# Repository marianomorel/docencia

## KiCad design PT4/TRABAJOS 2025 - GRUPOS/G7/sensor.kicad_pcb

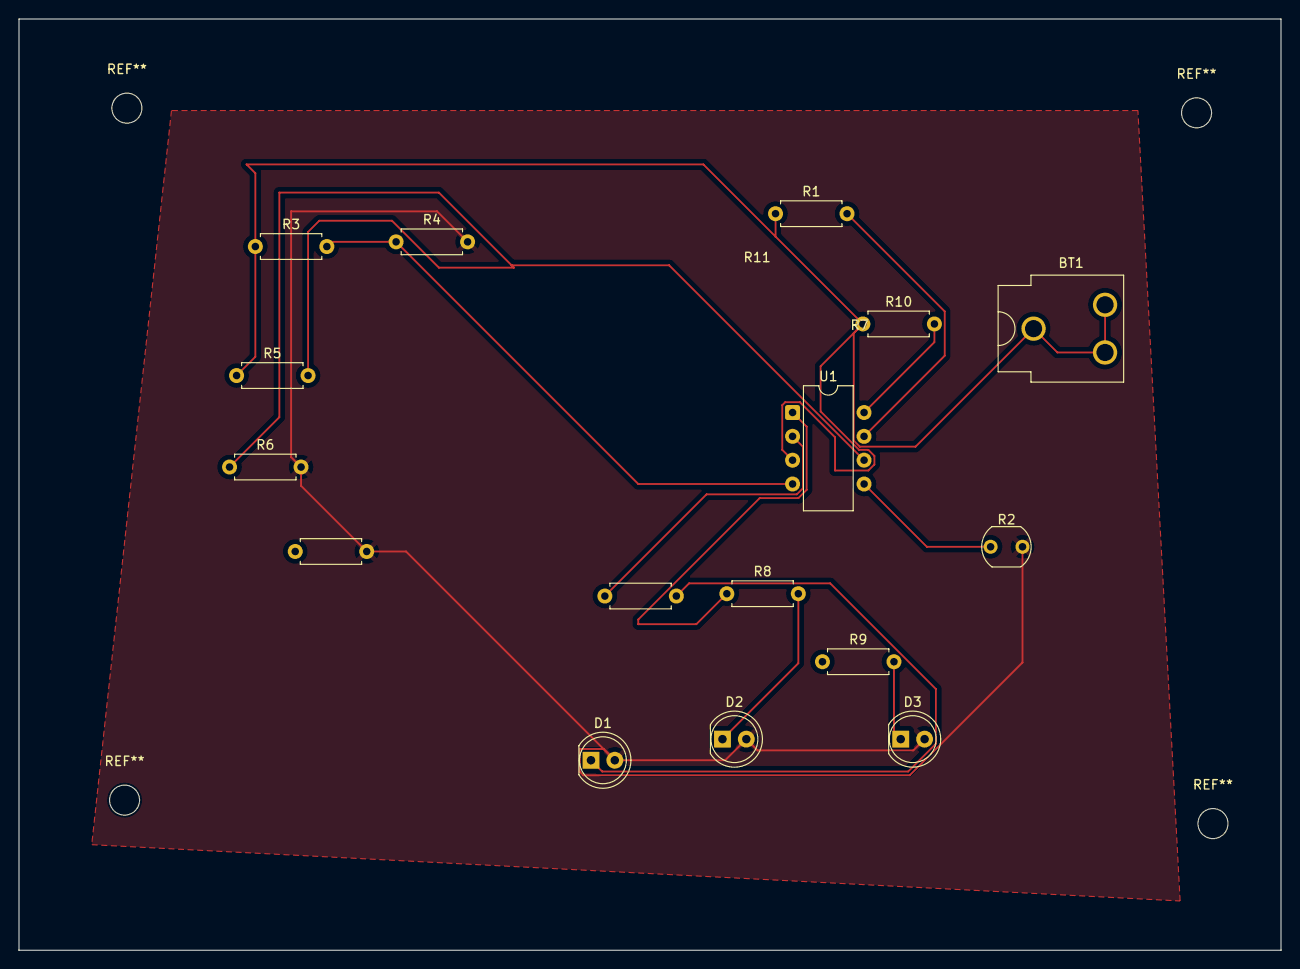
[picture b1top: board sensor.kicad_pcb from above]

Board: 2 copper layers, 134.5 x 99.2 mm, 16 parts (0 on the bottom side), 11 nets.

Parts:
BT1: Battery; BatteryClip_Keystone_54_D16-19mm
D1, D2, D3: LED; LED_D5.0mm
R1, R3, R4, R5, R6, R7, R8, R9, R10, R11: R; R_Axial_DIN0207_L6.3mm_D2.5mm_P7.62mm_Horizontal
R2: LDR07; R_LDR_5.1x4.3mm_P3.4mm_Vertical
U1: LM339; CERDIP-8_W7.62mm_SideBrazed

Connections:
Earth: D1.2 (A), D2.2 (A), D3.2 (A), R2.2, R4.2, R6.2, R11.2
unnamed: BT1.1 (+), R1.1, R3.1, R5.1, R10.1, U1.3 (V+)
unnamed: D1.1 (K), R7.2
unnamed: D2.1 (K), R8.2
unnamed: D3.1 (K), R9.2
unnamed: R7.1, U1.2
unnamed: R8.1, U1.1
unnamed: R1.2, R2.1, U1.5 (+), U1.7 (+)
unnamed: R3.2, R4.1, U1.4 (-)
unnamed: R5.2, R6.1, U1.6 (-)
unnamed: R10.2, U1.8 (-)

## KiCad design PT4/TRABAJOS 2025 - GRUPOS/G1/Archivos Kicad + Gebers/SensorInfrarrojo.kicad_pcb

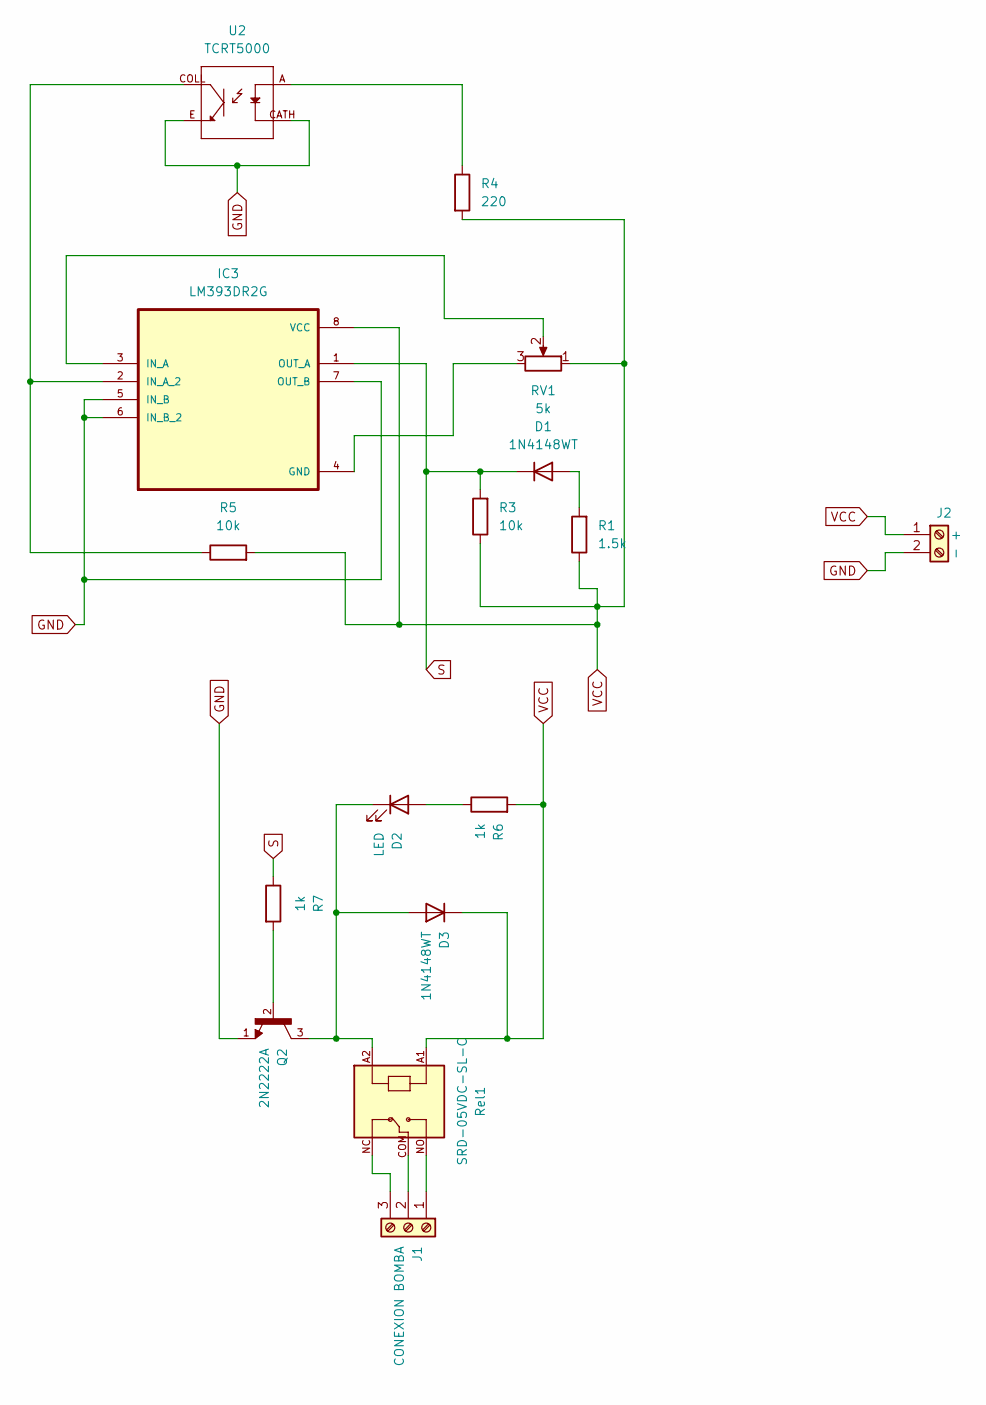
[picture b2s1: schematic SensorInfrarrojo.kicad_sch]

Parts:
D1, D3: 1N4148WT; D_SOD-523
D2: LED; LED_0402_1005Metric_Pad0.77x0.64mm_HandSolder
IC3: LM393DR2G; SOIC127P600X265-8N
J1: CONEXION BOMBA; TerminalBlock_Phoenix_MKDS-1,5-3_1x03_P5.00mm_Horizontal
J2: - +; TerminalBlock_MaiXu_MX126-5.0-02P_1x02_P5.00mm
Q2: 2N2222A; TO92254P470H750-3; PARTREV N/A
R1: 1.5k; R_0603_1608Metric_Pad0.98x0.95mm_HandSolder
R3, R5: 10k; R_0603_1608Metric_Pad0.98x0.95mm_HandSolder
R4: 220; R_0603_1608Metric_Pad0.98x0.95mm_HandSolder
R6, R7: 1k; R_Axial_DIN0204_L3.6mm_D1.6mm_P5.08mm_Horizontal
RV1: 5k; Potentiometer_Bourns_3296W_Vertical
Rel1: SRD-05VDC-SL-C; RELAY_SRD-05VDC-SL-C
U2: TCRT5000; OPTO_TCRT5000; PARTREV 1.7

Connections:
GND: IC3.5 (IN_B), IC3.6 (IN_B_2), IC3.7 (OUT_B), J2.2, Q2.1, U2.CATH, U2.E
unnamed: D1.2 (A), R1.2
unnamed: D2.2 (A), R6.1
unnamed: D2.1 (K), D3.2 (A), Q2.3, Rel1.A2
unnamed: IC3.4 (GND), RV1.3
unnamed: IC3.3 (IN_A), RV1.2
unnamed: IC3.2 (IN_A_2), R5.1, U2.COLL
unnamed: J1.1, Rel1.NO
unnamed: J1.2, Rel1.COM
unnamed: J1.3, Rel1.NC
unnamed: Q2.2, R7.2
unnamed: R4.1, U2.A
S: D1.1 (K), IC3.1 (OUT_A), R3.2, R7.1
VCC: D3.1 (K), IC3.8 (VCC), J2.1, R1.1, R3.1, R4.2, R5.2, R6.2, RV1.1, Rel1.A1

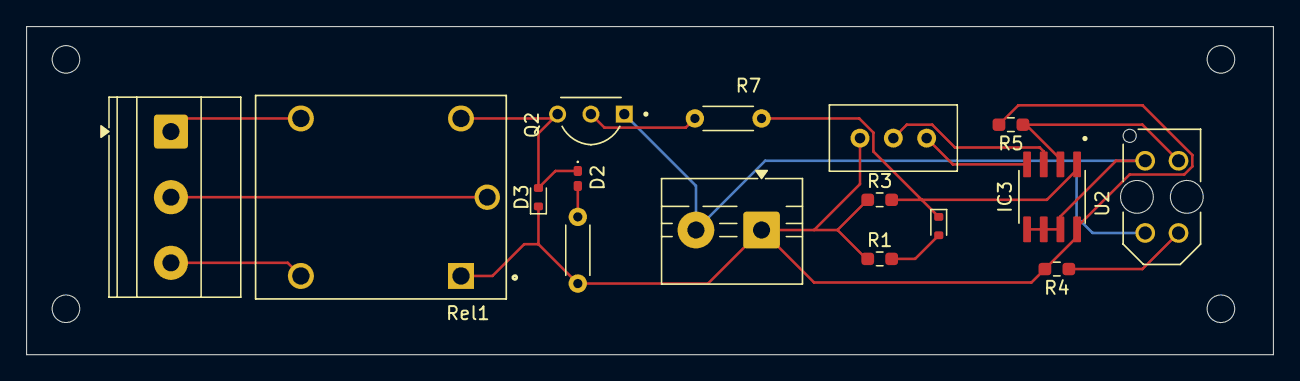
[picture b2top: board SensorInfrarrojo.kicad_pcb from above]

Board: 2 copper layers, 95.0 x 25.0 mm, 16 parts (0 on the bottom side), 14 nets.

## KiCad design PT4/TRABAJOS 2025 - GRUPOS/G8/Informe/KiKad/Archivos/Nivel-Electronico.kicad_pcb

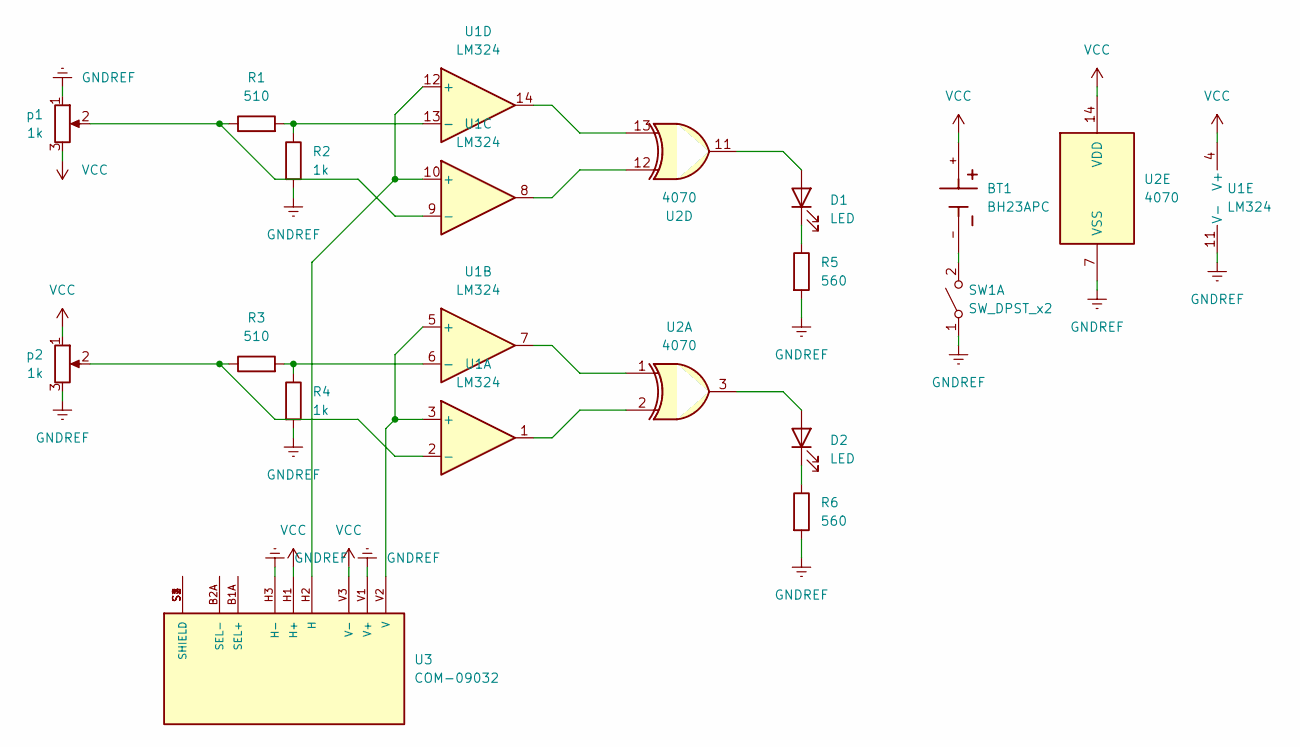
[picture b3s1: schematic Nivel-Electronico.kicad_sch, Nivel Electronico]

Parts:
BT1: BH23APC; BAT_BH23APC
D1, D2: LED; LED_D5.0mm
R1, R3: 510; R_Axial_DIN0204_L3.6mm_D1.6mm_P5.08mm_Vertical
R2, R4: 1k; R_Axial_DIN0204_L3.6mm_D1.6mm_P5.08mm_Vertical
R5, R6: 560; R_Axial_DIN0204_L3.6mm_D1.6mm_P5.08mm_Vertical
SW1: SW_DPST_x2; SW_Push_2P2T_Toggle_CK_PVA2OAH5xxxxxxV2
U1: LM324; DIP-14_W7.62mm_LongPads
U2: 4070; DIP-14_W7.62mm_LongPads
U3: COM-09032; XDCR_COM-09032
p1, p2: 1k; Potentiometer_ACP_CA9-V10_Vertical

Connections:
GNDREF: R2.2, R4.2, R5.2, R6.2, SW1.1 (A), U1.11 (V-), U2.7 (VSS), U3.H3 (H-), U3.V1 (V+), p1.1, p2.3
unnamed: D1.2 (A), U2.11
unnamed: D1.1 (K), R5.1
unnamed: D2.2 (A), U2.3
unnamed: D2.1 (K), R6.1
unnamed: BT1.-, SW1.2 (B)
unnamed: U1.1, U2.2
unnamed: U1.7, U2.1
unnamed: U1.8, U2.12
unnamed: U1.14, U2.13
unnamed: U1.3 (+), U1.5 (+), U3.V2 (V)
unnamed: R3.1, U1.2 (-), p2.2
unnamed: R3.2, R4.1, U1.6 (-)
unnamed: U1.10 (+), U1.12 (+), U3.H2 (H)
unnamed: R1.1, U1.9 (-), p1.2
unnamed: R1.2, R2.1, U1.13 (-)
unnamed: U3.S1 (SHIELD), U3.S2 (SHIELD), U3.S3 (SHIELD), U3.S4 (SHIELD)
VCC: BT1.+, U1.4 (V+), U2.14 (VDD), U3.H1 (H+), U3.V3 (V-), p1.3, p2.1

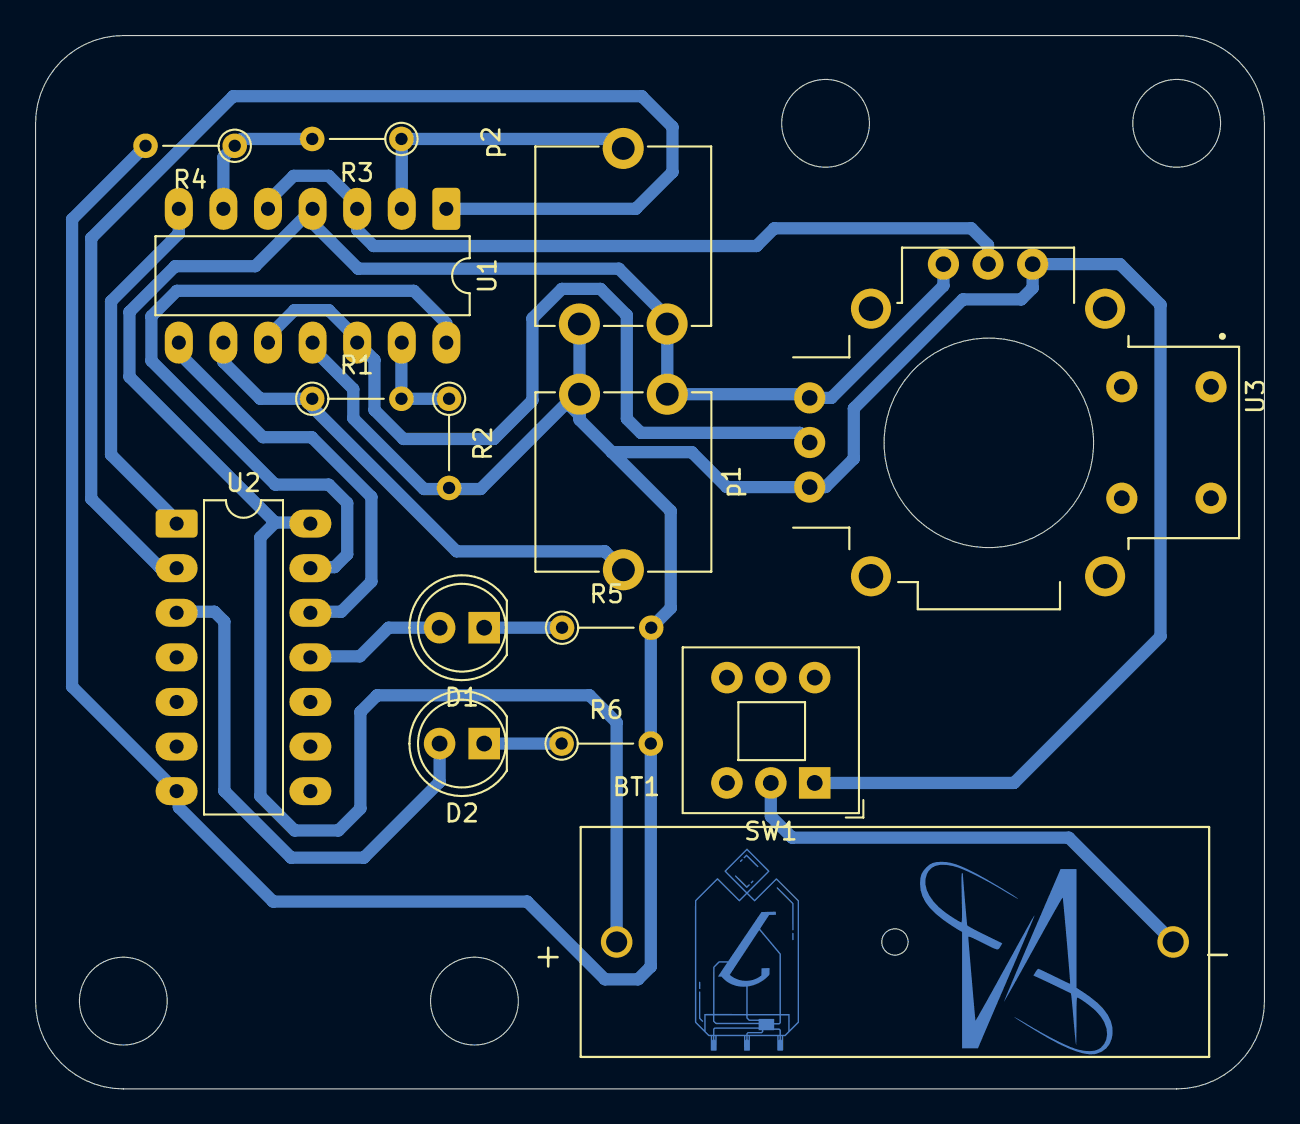
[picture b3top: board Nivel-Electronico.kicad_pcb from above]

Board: 2 copper layers, 70.0 x 60.0 mm, 15 parts (0 on the bottom side), 18 nets.

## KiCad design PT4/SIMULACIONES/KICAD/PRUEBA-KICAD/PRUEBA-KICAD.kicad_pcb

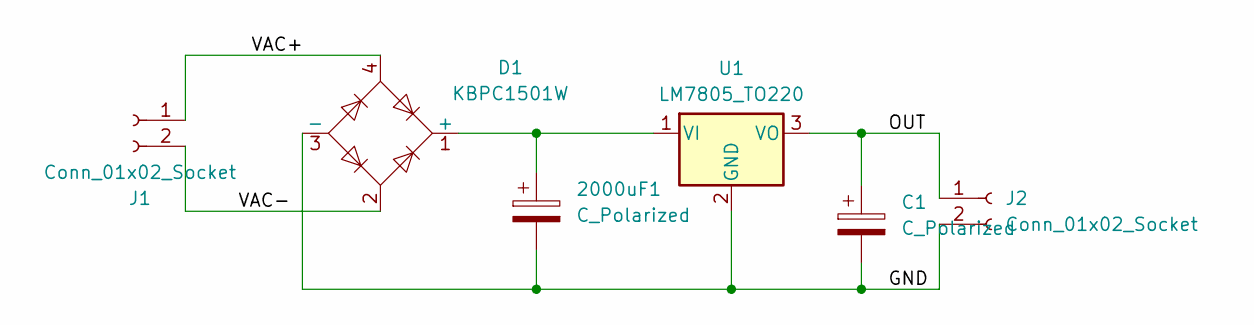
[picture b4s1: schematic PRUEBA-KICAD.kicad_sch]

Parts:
2000uF1: C_Polarized; C_Radial_D18.0mm_H35.5mm_P7.50mm
C1: C_Polarized; C_Radial_D5.0mm_H11.0mm_P2.00mm
D1: KBPC1501W; Diode_Bridge_GeneSiC_KBPC_W
J1, J2: Conn_01x02_Socket; TerminalBlock_MaiXu_MX126-5.0-02P_1x02_P5.00mm
U1: LM7805_TO220; TO-220-3_Vertical

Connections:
/GND: 2000uF1.2, C1.2, D1.3 (-), J2.2, U1.2 (GND)
/OUT: C1.1, J2.1, U1.3 (VO)
/VAC+: D1.4, J1.1
/VAC-: D1.2, J1.2
unnamed: 2000uF1.1, D1.1 (+), U1.1 (VI)

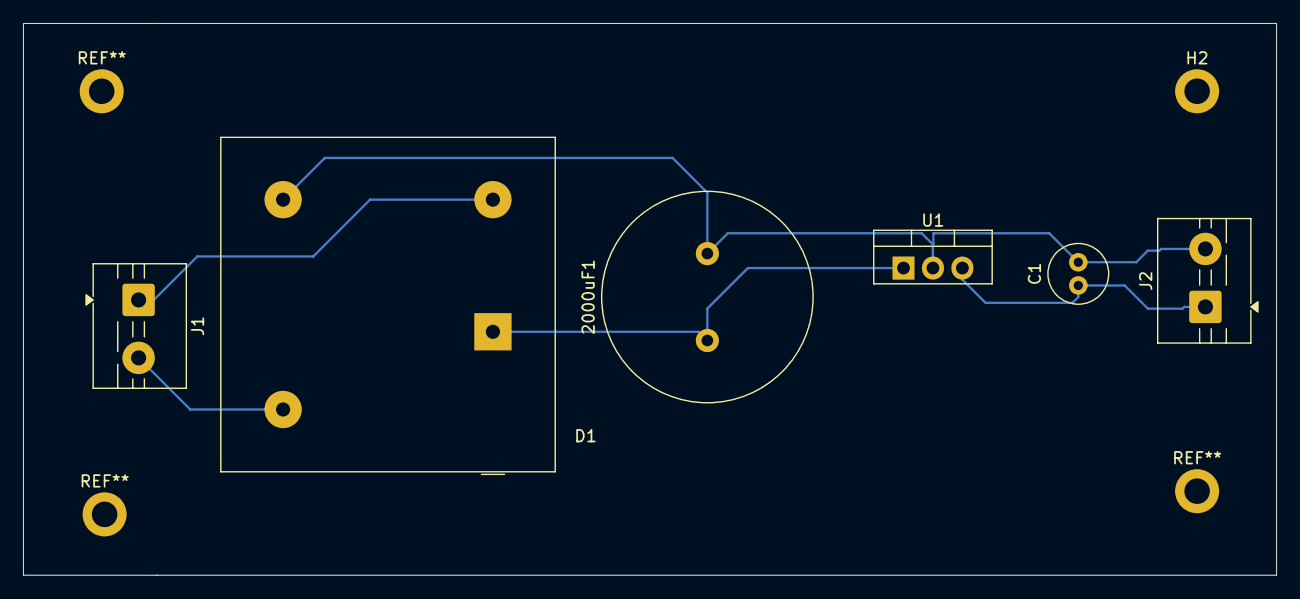
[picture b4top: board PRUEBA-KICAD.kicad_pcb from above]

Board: 2 copper layers, 108.1 x 47.6 mm, 7 parts (0 on the bottom side), 5 nets.

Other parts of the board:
H2: MountingHole_2.2mm_M2_DIN965_Pad

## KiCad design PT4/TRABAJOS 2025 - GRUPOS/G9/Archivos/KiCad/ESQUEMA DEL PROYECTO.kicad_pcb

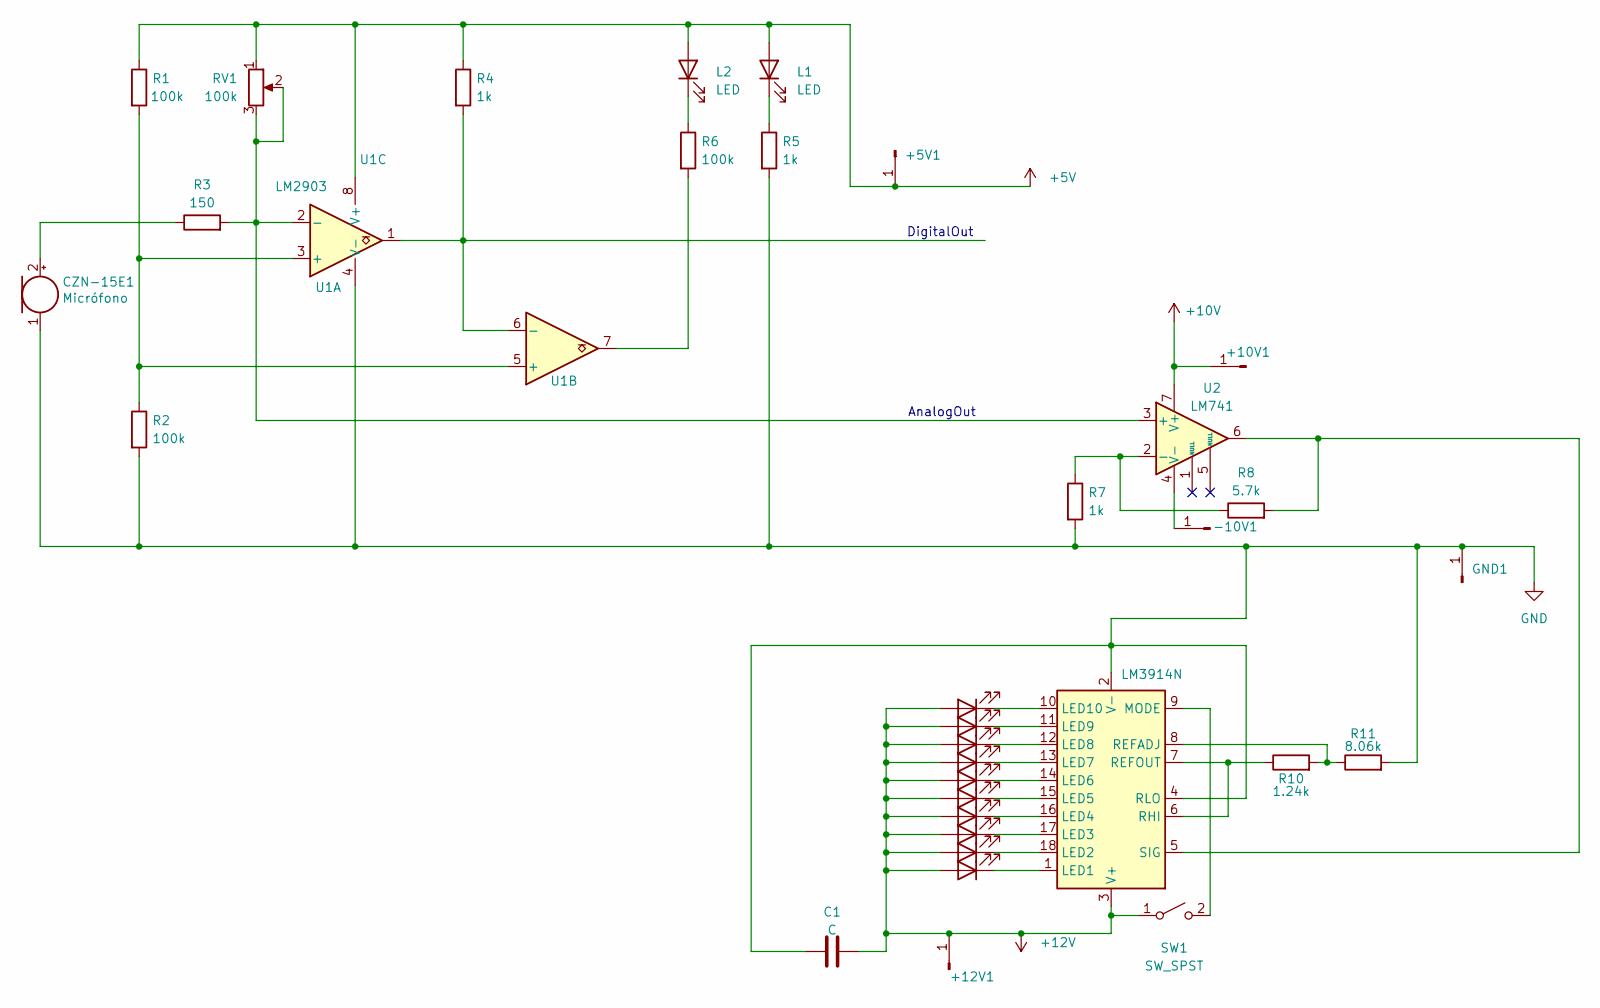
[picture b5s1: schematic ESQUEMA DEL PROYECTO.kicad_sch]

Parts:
+5V1, +10V1, +12V1: Conn_01x01_Pin; TestPoint_Pad_D3.0mm
-10V1: Conn_01x01_Pin; TestPoint_Pad_D3.0mm
C1: C; CP_EIA-1608-08_AVX-J
CZN-15E1: Micrófono; POM-2244P-C3310-2-R
GND1: Conn_01x01_Pin; TestPoint_Pad_D3.0mm
L1, L2, L3, L4, L5, L6, L7, L8, L9, L10, L11, L12: LED; LED_0603_1608Metric
R1, R2, R6: 100k; R_0805_2012Metric
R3: 150; R_0805_2012Metric
R4, R5, R7: 1k; R_0805_2012Metric
R8: 5.7k; R_0805_2012Metric
R10: 1.24k; R_0805_2012Metric
R11: 8.06k; R_0805_2012Metric
RV1: 100k; Potentiometer_Bourns_3296X_Horizontal
SW1: SW_SPST; SW_SPST_TL3342
U1: LM2903; DIP-8_W7.62mm
U2: LM741; DIP-8_W7.62mm
U3: LM3914N; DIP-18_W7.62mm

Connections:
+5V: +5V1.1, L1.2 (A), L2.2 (A), R1.1, R4.1, RV1.1, U1.8 (V+)
+10V: +10V1.1, U2.7 (V+)
+12V: +12V1.1, C1.2, L3.2 (A), L4.2 (A), L5.2 (A), L6.2 (A), L7.2 (A), L8.2 (A), L9.2 (A), L10.2 (A), L11.2 (A), L12.2 (A), SW1.1 (A), U3.3 (V+)
GND: C1.1, CZN-15E1.1 (-), GND1.1, R2.2, R5.2, R7.2, R11.2, U1.4 (V-), U3.2 (V-), U3.4 (RLO)
unnamed: -10V1.1, U2.4 (V-)
unnamed: CZN-15E1.2 (+), R3.1
unnamed: L1.1 (K), R5.1
unnamed: L2.1 (K), R6.1
unnamed: L3.1 (K), U3.1 (LED1)
unnamed: L4.1 (K), U3.18 (LED2)
unnamed: L5.1 (K), U3.17 (LED3)
unnamed: L6.1 (K), U3.16 (LED4)
unnamed: L7.1 (K), U3.15 (LED5)
unnamed: L8.1 (K), U3.14 (LED6)
unnamed: L9.1 (K), U3.13 (LED7)
unnamed: L10.1 (K), U3.12 (LED8)
unnamed: L11.1 (K), U3.11 (LED9)
unnamed: L12.1 (K), U3.10 (LED10)
unnamed: R6.2, U1.7
unnamed: SW1.2 (B), U3.9 (MODE)
unnamed: R1.2, R2.1, U1.3 (+), U1.5 (+)
unnamed: R3.2, RV1.2, RV1.3, U1.2 (-), U2.3 (+)
unnamed: R4.2, U1.1, U1.6 (-)
unnamed: R7.1, R8.1, U2.2 (-)
unnamed: R10.2, R11.1, U3.8 (REFADJ)
unnamed: R10.1, U3.6 (RHI), U3.7 (REFOUT)
unnamed: R8.2, U2.6, U3.5 (SIG)

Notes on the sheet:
AnalogOut
DigitalOut

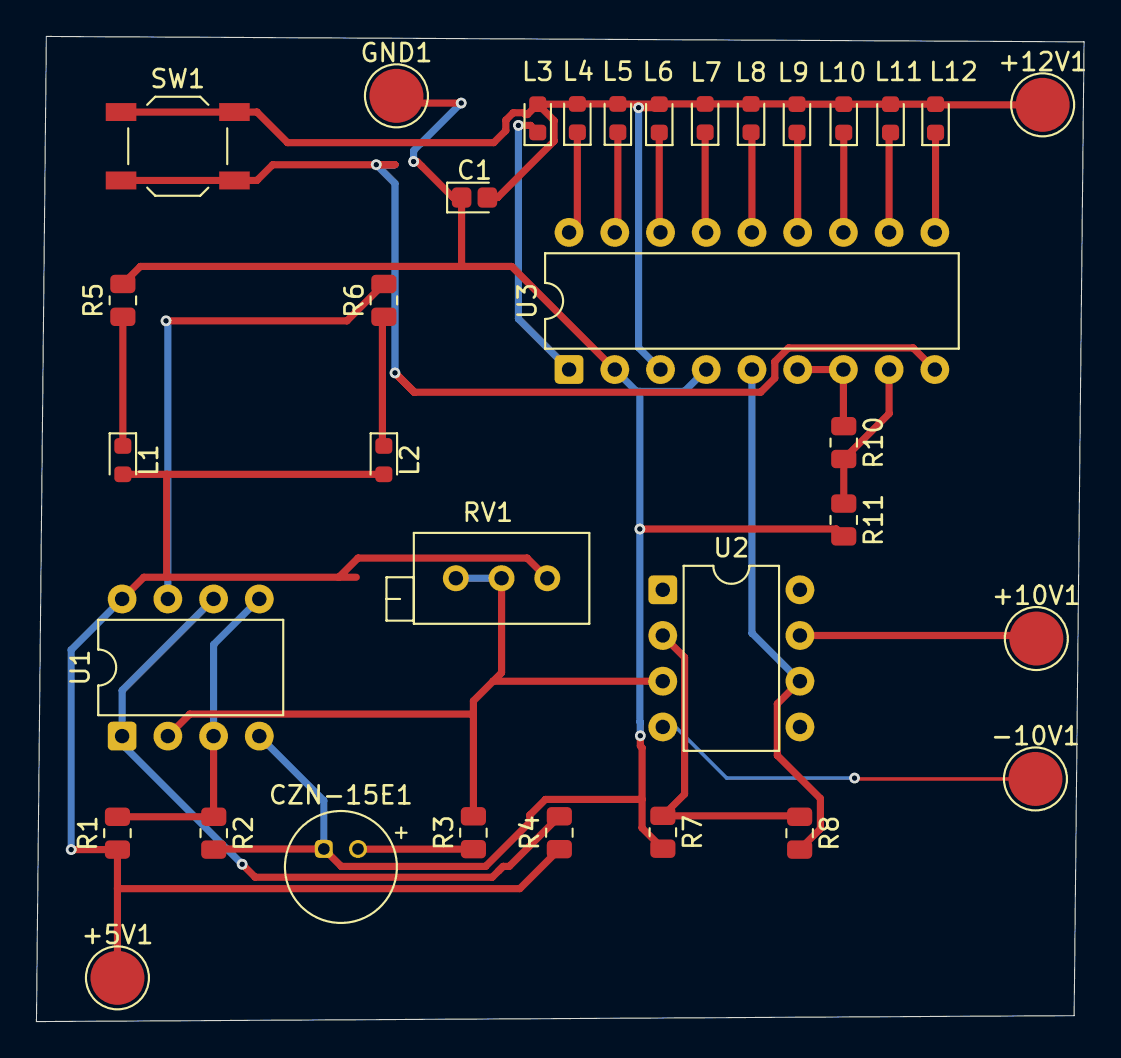
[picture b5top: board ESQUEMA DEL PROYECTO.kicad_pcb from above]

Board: 2 copper layers, 58.2 x 54.7 mm, 34 parts (0 on the bottom side), 27 nets.

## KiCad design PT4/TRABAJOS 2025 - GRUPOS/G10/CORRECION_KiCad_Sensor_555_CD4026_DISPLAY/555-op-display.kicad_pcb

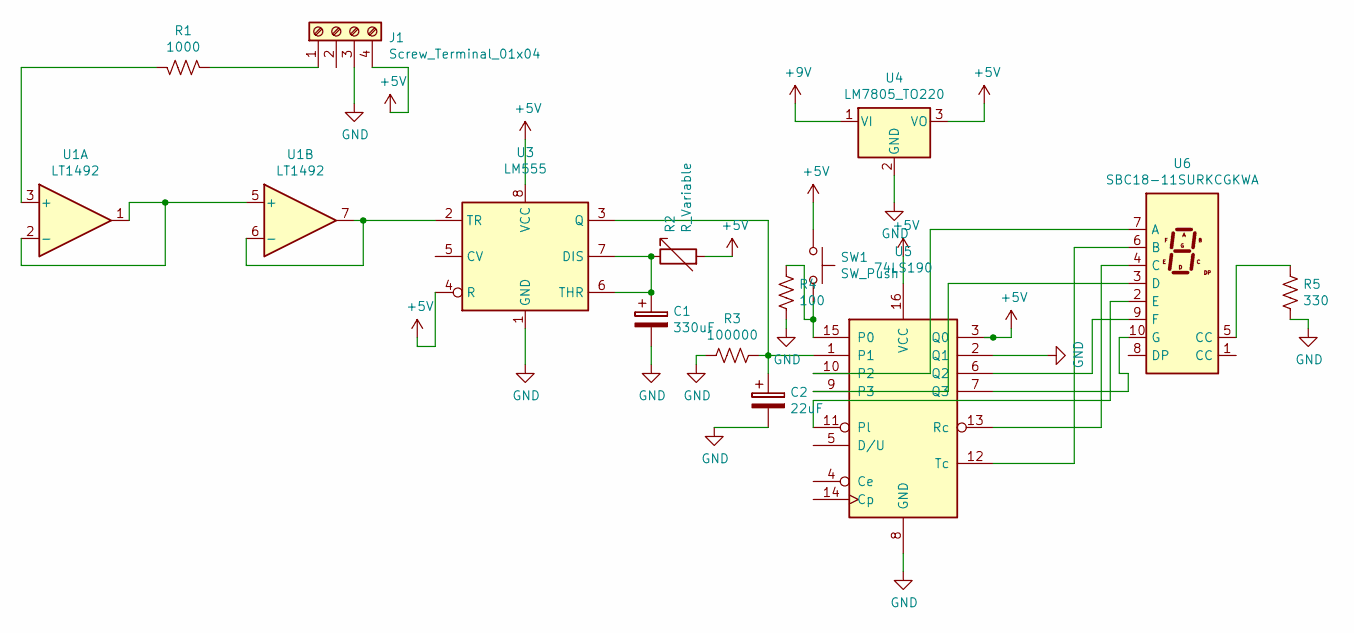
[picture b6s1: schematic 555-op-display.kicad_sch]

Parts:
C1: 330uF; CP_Radial_D5.0mm_P2.50mm
C2: 22uF; CP_Radial_D5.0mm_P2.50mm
J1: Screw_Terminal_01x04; TerminalBlock_bornier-4_P5.08mm
R1: 1000; R_Axial_DIN0204_L3.6mm_D1.6mm_P5.08mm_Horizontal
R2: R_Variable; Potentiometer_Trimmer_ACP_CA6v_Horizontal
R3: 100000; R_Axial_DIN0207_L6.3mm_D2.5mm_P7.62mm_Horizontal
R4: 100; R_Axial_DIN0207_L6.3mm_D2.5mm_P7.62mm_Horizontal
R5: 330; R_Axial_DIN0207_L6.3mm_D2.5mm_P7.62mm_Horizontal
SW1: SW_Push; KSA_Tactile_SPST
U1: LT1492; DIP-8_W7.62mm
U3: LM555; DIP-8_W7.62mm
U4: LM7805_TO220; TO-220-3_Vertical
U5: 74LS190; DIP-16_W7.62mm
U6: SBC18-11SURKCGKWA; 7SEGMENT-LED__HDSM531_HDSM533_SMD

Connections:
+5V: J1.4, R2.2, SW1.1, U3.4 (R), U3.8 (VCC), U4.3 (VO), U5.3 (Q0), U5.16 (VCC)
+9V: U4.1 (VI)
GND: C1.2, C2.2, J1.3, R3.2, R4.2, R5.2, U3.1 (GND), U4.2 (GND), U5.2 (Q1), U5.8 (GND)
unnamed: J1.1, R1.1
unnamed: R5.1, U6.5 (CC)
unnamed: R1.2, U1.3 (+)
unnamed: U1.1, U1.2 (-), U1.5 (+)
unnamed: U1.6 (-), U1.7, U3.2 (TR)
unnamed: C1.1, R2.1, U3.6 (THR), U3.7 (DIS)
unnamed: C2.1, R3.1, U3.3 (Q), U5.1
unnamed: R4.1, SW1.2, U5.15 (P0)
unnamed: U5.10 (P2), U6.7 (A)
unnamed: U5.9 (P3), U6.3 (D)
unnamed: U5.11 (Pl), U6.2 (E)
unnamed: U5.6 (Q2), U6.9 (F)
unnamed: U5.7 (Q3), U6.10 (G)
unnamed: U5.13 (Rc), U6.4 (C)
unnamed: U5.12 (Tc), U6.6 (B)

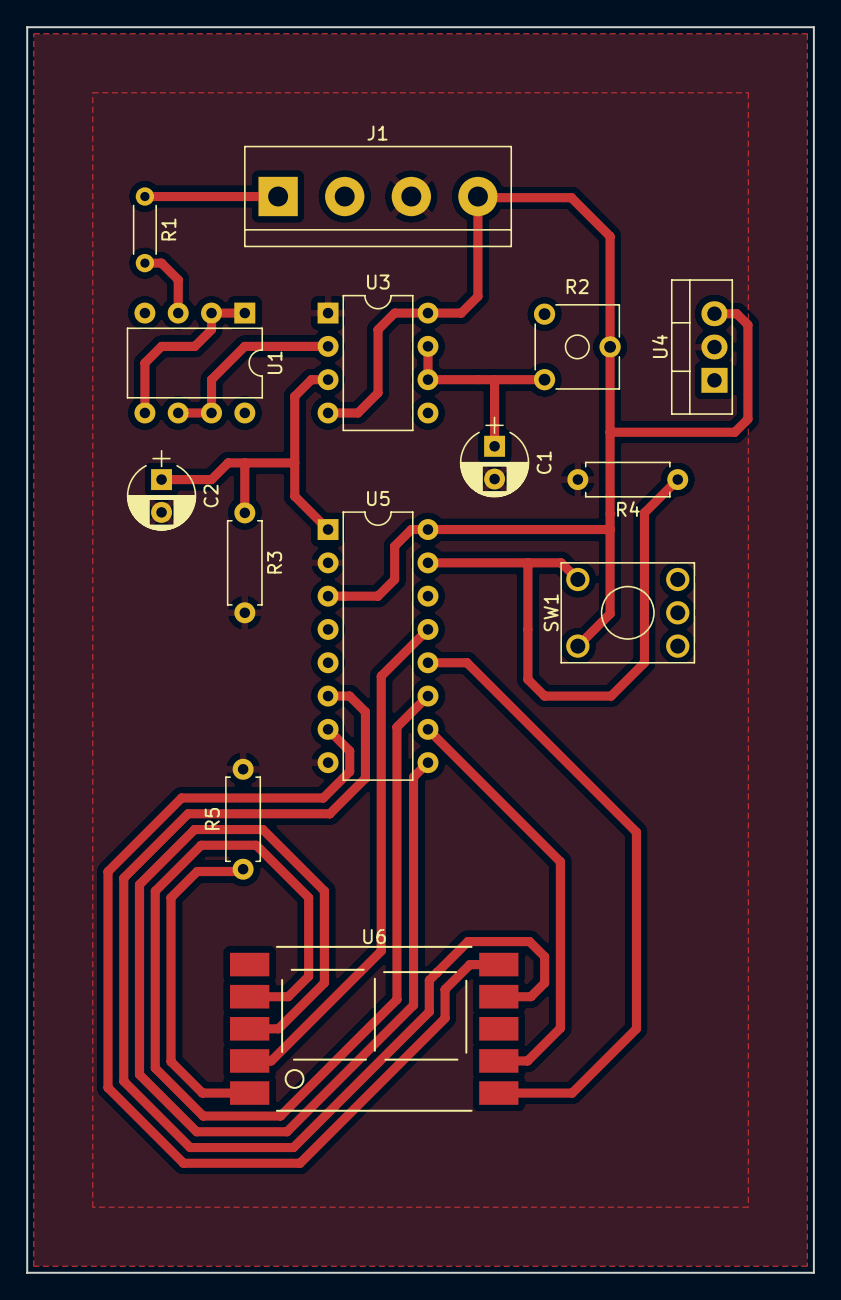
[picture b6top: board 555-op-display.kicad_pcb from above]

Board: 2 copper layers, 60.0 x 95.0 mm, 14 parts (0 on the bottom side), 17 nets.

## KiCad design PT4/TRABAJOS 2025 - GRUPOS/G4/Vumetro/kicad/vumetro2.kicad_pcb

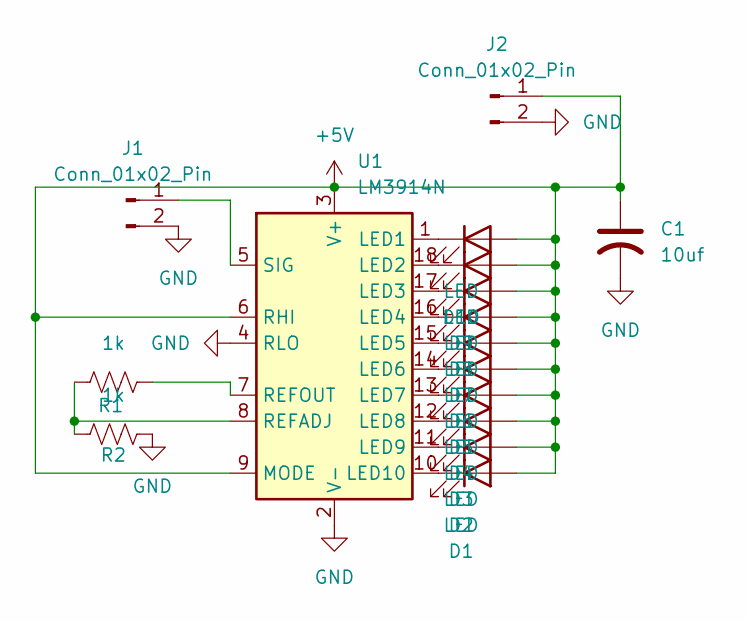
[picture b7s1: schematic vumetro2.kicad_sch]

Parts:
C1: 10uf; CP_Radial_D5.0mm_P2.00mm
D1, D2, D3, D4, D5, D6, D7, D8, D9, D10: LED; LED_D3.0mm_FlatTop
J1, J2: Conn_01x02_Pin; TerminalBlock_4Ucon_1x02_P3.50mm_Horizontal
R1, R2: 1k; R_Axial_DIN0204_L3.6mm_D1.6mm_P5.08mm_Horizontal
U1: LM3914N; DIP-18_W7.62mm

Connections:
+5V: C1.1, D1.2 (A), D2.2 (A), D3.2 (A), D4.2 (A), D5.2 (A), D6.2 (A), D7.2 (A), D8.2 (A), D9.2 (A), D10.2 (A), J2.1, U1.3 (V+), U1.6 (RHI), U1.9 (MODE)
GND: C1.2, J1.2, J2.2, R2.2, U1.2 (V-), U1.4 (RLO)
unnamed: D1.1 (K), U1.10 (LED10)
unnamed: D2.1 (K), U1.11 (LED9)
unnamed: D3.1 (K), U1.12 (LED8)
unnamed: D4.1 (K), U1.13 (LED7)
unnamed: D5.1 (K), U1.14 (LED6)
unnamed: D6.1 (K), U1.15 (LED5)
unnamed: D7.1 (K), U1.16 (LED4)
unnamed: D8.1 (K), U1.17 (LED3)
unnamed: D9.1 (K), U1.18 (LED2)
unnamed: D10.1 (K), U1.1 (LED1)
unnamed: J1.1, U1.5 (SIG)
unnamed: R1.1, R2.1, U1.8 (REFADJ)
unnamed: R1.2, U1.7 (REFOUT)

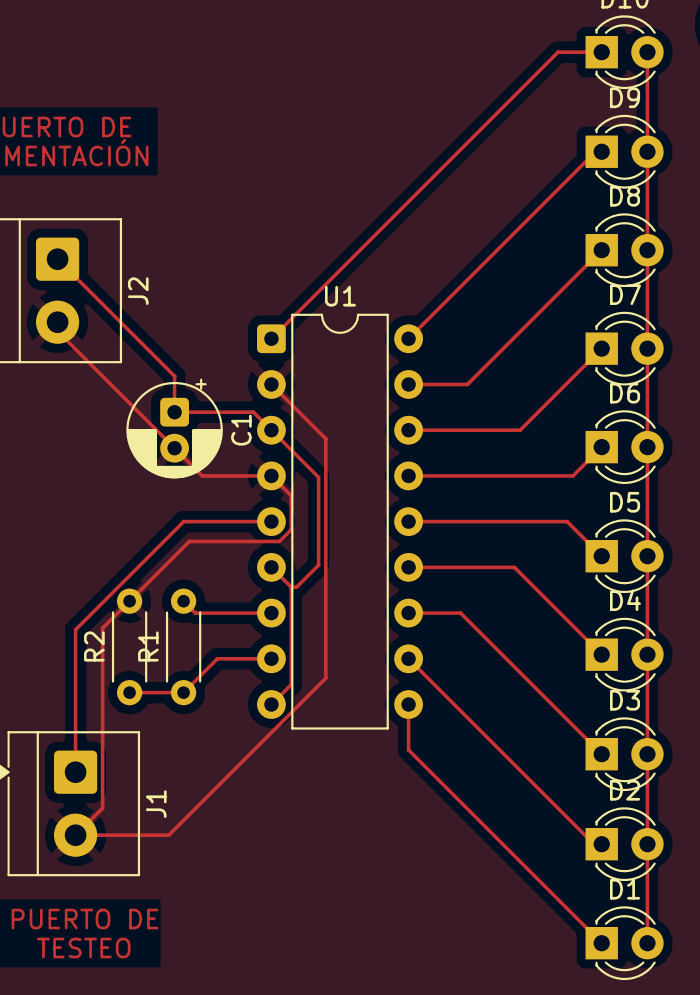
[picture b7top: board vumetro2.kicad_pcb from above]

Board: 2 copper layers, 16 parts (0 on the bottom side), 15 nets.

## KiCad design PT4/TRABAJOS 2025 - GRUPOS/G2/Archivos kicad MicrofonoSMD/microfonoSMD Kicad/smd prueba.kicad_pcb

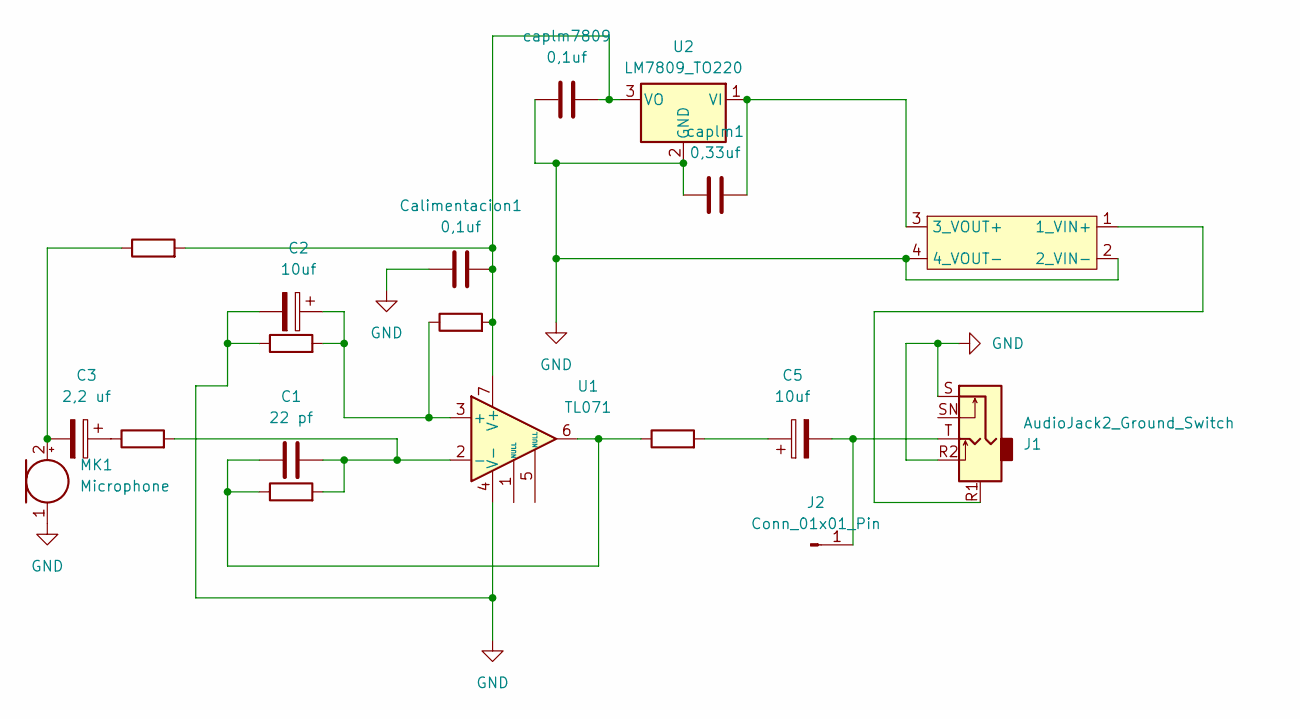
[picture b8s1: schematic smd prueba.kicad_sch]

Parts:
C1: 22 pf; C_0805_2012Metric_Pad1.18x1.45mm_HandSolder
C2, C5: 10uf; CP_Elec_4x5.4
C3: 2,2 uf; CP_Elec_4x5.4
Calimentacion1: 0,1uf; C_0805_2012Metric_Pad1.18x1.45mm_HandSolder
J1: AudioJack2_Ground_Switch; Jack_3.5mm_PJ320D_Horizontal
J2: Conn_01x01_Pin; PinHeader_1x01_P1.00mm_Vertical
MK1: Microphone; POM-2244P-C3310-2-R
R3: 2,2k; R_1206_3216Metric_Pad1.30x1.75mm_HandSolder
R5: 100; R_1206_3216Metric_Pad1.30x1.75mm_HandSolder
RP2: 200k; R_1206_3216Metric_Pad1.30x1.75mm_HandSolder
RP3: 10k; R_1206_3216Metric_Pad1.30x1.75mm_HandSolder
Ralimentacion1: 10k; R_1206_3216Metric_Pad1.30x1.75mm_HandSolder
Rpolarizadordeelectret1: 10k; R_1206_3216Metric_Pad1.30x1.75mm_HandSolder
U1: TL071; soic 8 personalizado
U2: LM7809_TO220; TO-252-2
U3: modulo mt3608
caplm1: 0,33uf; C_0805_2012Metric_Pad1.18x1.45mm_HandSolder
caplm7809: 0,1uf; C_0805_2012Metric_Pad1.18x1.45mm_HandSolder

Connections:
GND: C2.2, Calimentacion1.1, J1.R2, J1.S, MK1.1 (-), RP3.1, U1.4 (V-), U2.2 (GND), U3.2 (2_VIN-), U3.4 (4_VOUT-), caplm1.1, caplm7809.1
unnamed: C1.2, R5.1, RP2.1, U1.6
unnamed: C3.1, R3.1
unnamed: C5.1, R5.2
unnamed: C5.2, J1.T, J2.1
unnamed: C3.2, MK1.2 (+), Rpolarizadordeelectret1.1
unnamed: C2.1, RP3.2, Ralimentacion1.1, U1.3 (+)
unnamed: C1.1, R3.2, RP2.2, U1.2 (-)
unnamed: Calimentacion1.2, Ralimentacion1.2, Rpolarizadordeelectret1.2, U1.7 (V+), U2.3 (VO), caplm7809.2
unnamed: U2.1 (VI), U3.3 (3_VOUT+), caplm1.2
unnamed: J1.R1, U3.1 (1_VIN+)

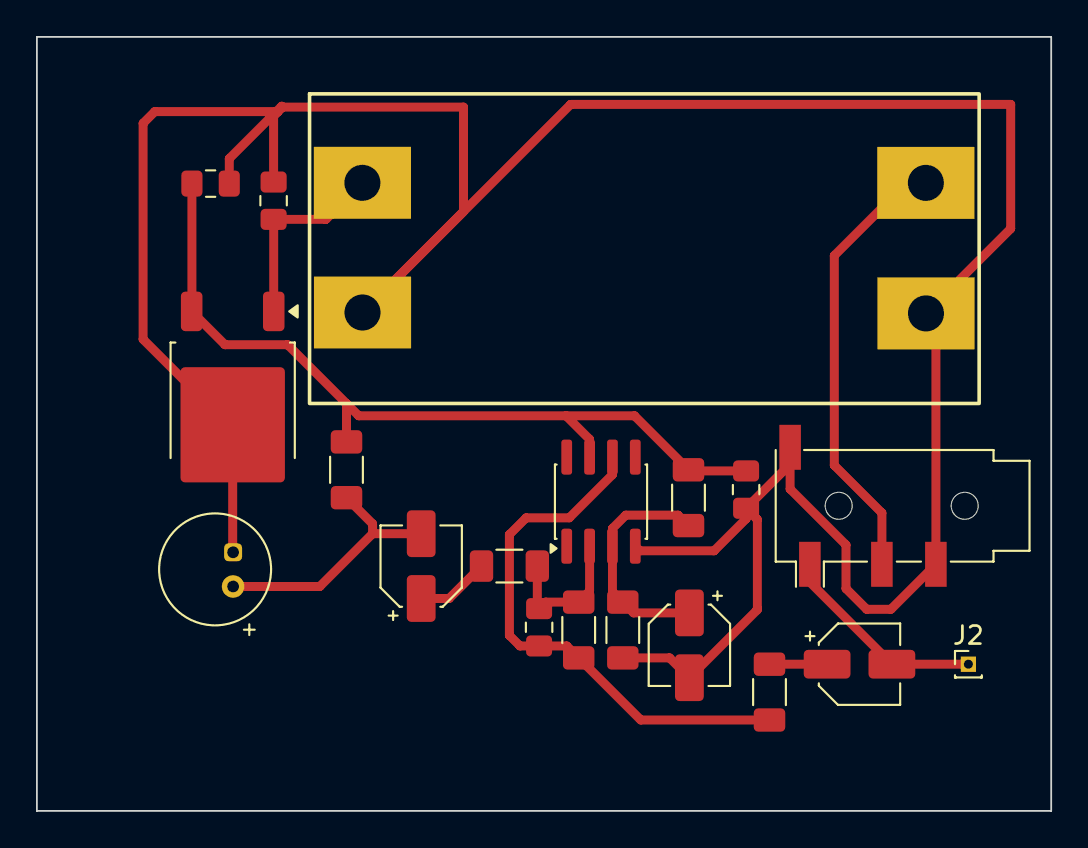
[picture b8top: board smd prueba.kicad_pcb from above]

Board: 2 copper layers, 56.3 x 43.0 mm, 19 parts (0 on the bottom side), 11 nets.

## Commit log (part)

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2026-03-20 Primer commit - Docencia limpio
2026-03-26 Actualizo puntero del submódulo G
